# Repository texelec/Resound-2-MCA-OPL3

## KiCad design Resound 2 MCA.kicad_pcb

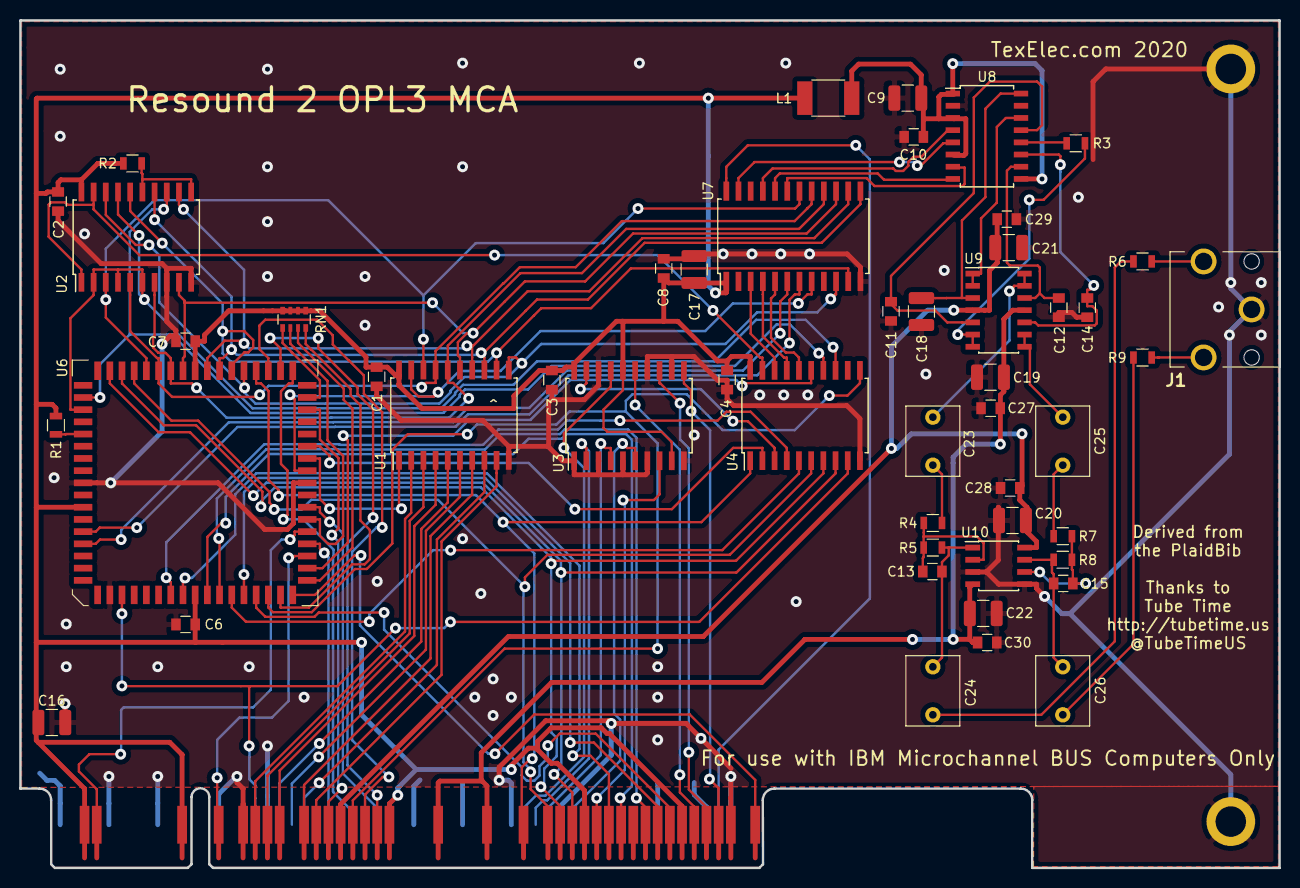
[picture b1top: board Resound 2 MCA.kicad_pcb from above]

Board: 2 copper layers, 131.1 x 88.3 mm, 53 parts (0 on the bottom side), 93 nets.

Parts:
C1, C2, C3, C4, C6, C7, C8, C10: 0.1uF; C_0805
C9, C16, C17, C19, C20, C21, C22: 10uF; C_1210_3225Metric
C11: 68pf; C_0805
C12, C14: 2.7nf; C_0805
C13, C15: 1n; C_0805
C18: 10uf; C_1210_3225Metric
C23, C24, C25, C26: 1uf; C_Rect_L7.2mm_W5.5mm_P5.00mm_FKS2_FKP2_MKS2_MKP2
C27, C28, C29, C30: 0.1uf; C_0805
J1: SJ1-3553NG; SJ13553NG
J2: BUS_MCA; BUS_MCA_ADLIB
L1: 820uh; L_1812
R1, R5, R8: 10K; R_0805
R2: 1K; R_0805
R3: 33; R_0805
R4, R7: 40K; R_0805
R6, R9: 100; R_0805
RN1: 10K; R_Array_Convex_4x0603
TP1, TP2: TestPoint; MH_125
U1: 74HCT245; SOIC-20W_7.5x12.8mm_Pitch1.27mm
U2: 74HCT244; SOIC-20W_7.5x12.8mm_Pitch1.27mm
U3: 74HCT688; SOIC-20W_7.5x12.8mm_Pitch1.27mm
U4: ATF16V8B; SOIC-20W_7.5x12.8mm_Pitch1.27mm
U6: P82C611; PLCC-68
U7: YMF262; SOIC-24W_7.5x15.4mm_Pitch1.27mm
U8: YAC512; SOIC-16W_5.3x10.2mm_Pitch1.27mm
U9: TL074; SOIC-14_3.9x8.7mm_Pitch1.27mm
U10: TL072; SOIC-8_3.9x4.9mm_Pitch1.27mm

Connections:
+5V: C1.1, C2.1, C3.1, C4.1, C6.1, C7.1, C8.2, C9.1, C10.2, C16.1, C17.1, J2.A7, J2.A15, J2.A31, J2.A48, J2.A56, L1.1, L1.2, R1.1, R2.1, RN1.1, RN1.2, RN1.3, RN1.4, U1.20, U2.20, U3.9, U3.16, U3.20, U4.20, U6.3, U6.18, U6.52, U7.1, U8.1, U8.3, U8.6, U8.9
+12V: C20.2, C21.1, C28.1, C29.1, J2.A35, U9.4, U10.8
-12V: C19.2, C22.1, C27.1, C30.1, J2.A23, J2.A27, U9.11, U10.4
/14.3M: J2.B4, U7.24
/A0: J2.A18, U4.6, U6.57
/A1: J2.A17, U4.7, U6.58
/A2: J2.A16, U4.8, U6.59
/A3: J2.A14, U3.8
/A4: J2.A13, U6.17
/A5: J2.A12, U6.19
/A6: J2.A10, U6.20
/A7: J2.A9, U6.22
/A8: J2.A8, U6.23
/A9: J2.A6, U3.15
/A10: J2.A5, U3.13
/A11: J2.A4, U3.11
/A12: J2.B20, U3.17
/A13: J2.B19, U3.2
/A14: J2.B18, U3.4
/A15: J2.B16, U3.6
/AOUT: C11.2, U8.13, U9.5
/BUFDIR: U1.1, U6.37
/CDEN: U4.2, U6.38
/CH1: C12.1, U8.10, U9.12
/CH2: C14.1, U8.11, U9.10
/CHRESET: J2.B42, U4.9, U6.12
/CV: C18.1, U8.16, U9.3
/D0: U1.11, U2.18, U6.48, U7.10
/D1: U1.12, U2.16, U6.49, U7.11
/D2: U1.13, U2.14, U6.50, U7.13
/D3: U1.14, U2.12, U6.51, U7.14
/D4: U1.15, U2.9, U6.53, U7.15
/D5: U1.16, U2.7, U6.54, U7.16
/D6: U1.17, U2.5, U6.55, U7.17
/D7: U1.18, U2.3, U6.56, U7.18
/ID_~OE: U2.1, U2.19, U4.19
/LEFT: J1.2, R6.1
/MP: U8.14, U9.1, U9.2
/M_~IO: J2.A34, U4.11, U6.24
/RIGHT: J1.3, R9.1
/SWIN: R3.2, U8.12
/YM_A0: U4.17, U7.4
/YM_A1: U4.16, U7.5
/YM_~IC: U4.18, U7.3
/~100RD: U2.13, U4.14, U6.62
/~101RD: U2.2, U2.4, U2.6, U2.17, U4.13, U6.63
/~688: U3.19, U4.3
/~ADL: J2.A20, U4.1, U6.47
/~BUFENL: U1.19, U6.36, U7.8
/~CD_SEL: U4.15, U6.28
/~MATCH103HI: U4.4, U6.16
/~MATCHA: U4.5, U6.21
/~RD: U6.5, U7.7
/~WR: U6.6, U7.6
DB0: J2.A37, U1.9
DB1: J2.B38, U1.8
DB2: J2.A38, U1.7
DB3: J2.B39, U1.6
DB4: J2.B40, U1.5
DB5: J2.A40, U1.4
DB6: J2.A41, U1.3
DB7: J2.A42, U1.2
GND: C1.2, C2.2, C3.2, C4.2, C6.2, C7.2, C8.1, C9.2, C10.1, C11.1, C12.2, C14.2, C16.2, C17.2, C18.2, C19.1, C20.1, C21.2, C22.2, C27.2, C28.2, C29.2, C30.2, J1.1, J2.A3, J2.A43, J2.B3, J2.B5, J2.B9, J2.B17, J2.B21, J2.B25, J2.B29, J2.B41, J2.B45, J2.B50, J2.B54, J2.B58, TP1.1, TP2.1, U1.10, U2.8, U2.10, U3.1, U3.3, U3.5, U3.7, U3.10, U3.12, U3.14, U3.18, U4.10, U6.1, U6.11, U6.35, U7.12, U8.2, U10.3, U10.5
unnamed: C13.1, R4.1, R5.2, U10.2
unnamed: C13.2, C24.2, R5.1, U10.1
unnamed: C15.1, C26.2, R8.1, U10.7
unnamed: C15.2, R7.1, R8.2, U10.6
unnamed: C23.1, R4.2
unnamed: C23.2, U9.13, U9.14
unnamed: C24.1, R6.2
unnamed: C25.1, R7.2
unnamed: C25.2, U9.8, U9.9
unnamed: C26.1, R9.2
unnamed: J2.A1, U6.26
unnamed: J2.A32, U6.45
unnamed: J2.A33, U6.46
unnamed: J2.A36, U6.41
unnamed: J2.A45, U6.29
unnamed: J2.A55, U6.31
unnamed: J2.B32, U6.33
unnamed: J2.B34, U6.44
unnamed: J2.B36, U6.30
unnamed: R1.2, U6.65
unnamed: R2.2, U2.11, U2.15
unnamed: R3.1, U9.6, U9.7
unnamed: RN1.5, U6.42
unnamed: RN1.6, U6.32
unnamed: RN1.7, U6.27
unnamed: RN1.8, U6.25
unnamed: U7.19, U8.7
unnamed: U7.20, U8.8
unnamed: U7.21, U8.4
unnamed: U7.23, U8.5

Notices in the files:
Resound 2 MCA.kicad_pcb:
Copyright (C) 2019 Eric Schlaepfer
License. See https://creativecommons.org/licenses/by-sa/4.0
This work is licensed under a Creative Commons Attribution-ShareAlike 4.0 International
